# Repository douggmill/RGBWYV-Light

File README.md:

# RGBWYV-Light

RGBWYV-Light is a six-channel LED lamp — red, green, blue, white, amber, and violet — built around two [Seeed XIAO nRF52840](https://wiki.seeedstudio.com/XIAO_BLE/) boards. A Tkinter desktop console talks USB CDC at 921600 baud to a BLE central remote, which bridges newline-terminated ASCII commands over BLE UART to the peripheral light.

- [Features](#features)
- [Architecture](#architecture)
- [Hardware](#hardware)
- [Bill of materials](#bill-of-materials)
- [Hardware status](#hardware-status)
- [Serial command reference](#serial-command-reference)
- [Saved data format](#saved-data-format)
- [Building and flashing](#building-and-flashing)
- [Console](#console)
- [Repository layout](#repository-layout)
- [Roadmap](#roadmap)
- [Contributing](#contributing)
- [License](#license)

## Features

- Four operating modes:
  - **0 — Classic RGB:** a red–green–blue rainbow swell
  - **1 — Audio:** seven-band MSGEQ7 visualization; the white channel stays off
  - **2 — Manual:** direct mixer for all six channels and PWM frequency
  - **3 — Color Swells (retro):** red–green–violet color swells
- AHT20 temperature sensing
- Fan control through a PCF8574 I/O expander at address `0x20`, with automatic hysteresis (on at 35 °C, off at 32 °C) plus manual `fan0` / `fan1` commands
- Save and load of the 59 mixer parameters and the current mode to the light's internal filesystem

## Architecture

```mermaid
flowchart LR
    Console["Tkinter console"] -->|"USB CDC, 921600 baud"| Remote["BLE central remote<br/>XIAO nRF52840 Sense"]
    Remote -->|"BLE UART"| Light["Peripheral light<br/>XIAO nRF52840"]
    Light --> PWM["Six-channel PWM<br/>R, G, B, W, Amber, Violet"]
    Light --> EQ["MSGEQ7 audio"]
    Light --> Sens["AHT20 and PCF8574 fan"]
```

The central remote identifies itself as `LED Console 001` (manufacturer `Doug's Garage`). The light reports model `LED Device 001` over the BLE Device Information Service. The console auto-detects the remote by sending `*idn` and matching the reply in `config.ini`.

## Hardware

The light uses a Seeed XIAO nRF52840 (plain, not Sense). The remote uses a Seeed XIAO nRF52840 Sense, and in the current firmware it is only a USB-to-BLE bridge — the central sketch does not drive header GPIO.

**All MCU header pins are 3.3 V only and are not 5 V tolerant.** The MSGEQ7 and any logic tied to those pins must run at 3.3 V or be level-shifted.

### Peripheral pin map

Verified from `RGB_Peripheral_Device_R2/main/main.ino`. On the Seeeduino nRF52 core, Arduino pin `n` is header `Dn`.

| Function | Firmware | Header pin |
|----------|----------|------------|
| Red PWM | `RED_PIN 7` | D7 |
| Green PWM | `GREEN_PIN 2` | D2 |
| Blue PWM | `BLUE_PIN 8` | D8 |
| White PWM | `WHITE_PIN 6` | D6 |
| Amber PWM | `AMBER_PIN 9` | D9 |
| Violet PWM | `VIOLET_PIN 3` | D3 |
| MSGEQ7 analog out | `analogPin A0` | A0 (D0) |
| MSGEQ7 reset | `resetPin 1` | D1 |
| MSGEQ7 strobe | `strobePin 10` | D10 |
| I2C SDA / SCL | default `Wire` | D4 / D5 |
| PCF8574 | `pcf.begin(0x20, &Wire)` | address `0x20`; fan on expander pin 2 |
| AHT20 | `Adafruit_AHTX0` on `Wire` | same I2C bus |

KiCad schematics, PCB, and Gerbers are in `RGBYVW_Schematic_PCB/`. The board includes MOSFET LED drivers, the MSGEQ7, and an AHT20.

PWM frequency is set by `adc55` (a value of 1000 = 10 kHz maximum) and is applied in manual and audio modes.

## Bill of materials

Main light board (`nRF52840_RGBWYV`), generated by KiCad from the schematic and grouped by value and footprint (52 parts). The CSV is [`RGBYVW_Schematic_PCB/BOM.csv`](RGBYVW_Schematic_PCB/BOM.csv); per-schematic BOMs and ERC/DRC reports are in [`RGBYVW_Schematic_PCB/reports/`](RGBYVW_Schematic_PCB/reports/). The original hand-written BOM, including the mechanical parts, is [`BOM_R3_source.txt`](RGBYVW_Schematic_PCB/BOM_R3_source.txt).

| Qty | References | Value | Footprint |
|----:|------------|-------|-----------|
| 1 | AHT20 | Conn_01x04 | `Connector_PinHeader_2.54mm:PinHeader_1x04_P2.54mm_Vertical` |
| 1 | C1 | 100uF | `Capacitor_THT:CP_Radial_D10.0mm_P3.80mm` |
| 1 | C2 | 33pF CoG 50V 0402 | `Capacitor_SMD:C_0402_1005Metric_Pad0.74x0.62mm_HandSolder` |
| 1 | C3 | 0.1uF CoG 50V 0704 | `Capacitor_SMD:C_0603_1608Metric_Pad1.08x0.95mm_HandSolder` |
| 1 | C4 | 22uF-10uF | `Capacitor_SMD:C_0603_1608Metric_Pad1.08x0.95mm_HandSolder` |
| 4 | C5-C8 | 0.1uF XR7 0603 | `Capacitor_SMD:C_0603_1608Metric_Pad1.08x0.95mm_HandSolder` |
| 2 | D1, D3 | SDM05U20S3-7 20V 500mA | `Diode_SMD:D_SOD-323_HandSoldering` |
| 1 | D2 | 12 pin LED | `KiCad User Library:12 pin LED` |
| 1 | J1 | Screw_Terminal_01x02 | `TerminalBlock:TerminalBlock_Xinya_XY308-2.54-2P_1x02_P2.54mm_Horizontal` |
| 1 | J2 | Screw_Terminal_01x03 | `TerminalBlock:TerminalBlock_Xinya_XY308-2.54-3P_1x03_P2.54mm_Horizontal` |
| 1 | J3 | Conn_01x04 (screw terminal) | `TerminalBlock:TerminalBlock_Xinya_XY308-2.54-4P_1x04_P2.54mm_Horizontal` |
| 1 | J4 | Fan WINSINN 2010 | `Connector_JST:JST_XH_B2B-XH-A_1x02_P2.50mm_Vertical` |
| 7 | Q1-Q7 | IRLML6244 | `Package_TO_SOT_SMD:SOT-23` |
| 2 | R1, R3 | 22kΩ | `Resistor_SMD:R_0603_1608Metric_Pad0.98x0.95mm_HandSolder` |
| 1 | R2 | 221kΩ 0805 | `Resistor_SMD:R_0805_2012Metric_Pad1.20x1.40mm_HandSolder` |
| 9 | R4-R9, R17-R19 | 10kΩ | `Resistor_SMD:R_0603_1608Metric_Pad0.98x0.95mm_HandSolder` |
| 6 | R10-R15 | 4.7Ω | `Resistor_THT:R_Axial_DIN0309_L9.0mm_D3.2mm_P12.70mm_Horizontal` |
| 1 | R16 | 100Ω | `Resistor_SMD:R_0603_1608Metric_Pad0.98x0.95mm_HandSolder` |
| 1 | U1 | L7805 | `Package_TO_SOT_THT:TO-220-3_Horizontal_TabDown` |
| 1 | U2 | MSGEQ7 | `Package_DIP:DIP-8_W7.62mm` |
| 1 | U3 | PCF8574T | `Package_SO:SOIC-16W_7.5x10.3mm_P1.27mm` |
| 6 | U4-U9 | LM317_TO-220 | `Package_TO_SOT_THT:TO-220-3_Vertical` |
| 1 | U10 | nRF52840_XAIO | `A_USER_FOOTPRINTS:XAIO-nRF528400-TTH` |

`D2` and `U10` use the project's custom KiCad parts (`User` / `A_USER_Library` symbols, `KiCad User Library` / `A_USER_FOOTPRINTS` footprints). The symbols and footprints are embedded in the schematic and board files, so they open and plot without the libraries; the standalone library files are not in this repo.

### Mechanical / hardware

From [`BOM_R3_source.txt`](RGBYVW_Schematic_PCB/BOM_R3_source.txt). Dimensions, fits and assembly notes are in [`mechanical/README.md`](mechanical/README.md).

| Item | Value / PN | Qty | Notes | Link |
|------|------------|----:|-------|------|
| Wooden box | Amazon part | 1 | 95.5 × 87 × 62 mm outer, 3 mm floor, 22 mm lid | [Amazon](https://www.amazon.com/dp/B0B51L68YK) |
| Reflector cone | Amazon part | 1 | 48 mm mouth, 12 mm LED hole; cut to 29.2 mm (flush with the lid) | [Amazon](https://www.amazon.com/dp/B07MS8N2DS) |
| Fan 30 × 30 × 10 mm | Sunon MF30100V1-1000U-A99 | 1 | 5 V, 24 mm holes (check voltage vs the circuit) | [Digi-Key](https://www.digikey.com/en/products/detail/sunon-fans/MF30100V1-1000U-A99/10441403) |
| Fan grill, 3D printed | `mechanical/parts/fan_grill_30mm.stl` | 1 | 36 × 36 × 2 mm, outside of the floor | |
| M3 flat-head screws + thin nuts (grill) | ISO 10642 / DIN 439 | 4 + 4 | M3 × 18 (grill 2 + floor 3 + fan 10) | |
| 2.1 mm DC jack | uxcell a14103100ux0223 | 1 | 2.1 × 5.5, M8 panel mount, 20 mm overall | [Amazon](https://www.amazon.com/dp/B01C8CRCJ4) |
| USB-C breakout (horizontal) | Amabro | 1 | Plate glued in its wall pocket | [Amazon](https://www.amazon.com/dp/B0H9S9C73Q) |
| 3.5 mm stereo jack (TRS) | CESS 318 | 1 | M6 panel mount, 20 mm overall | [Amazon](https://www.amazon.com/dp/B00ZYWILMS) |
| Screw terminals 2.54 mm (J1 2P, J2 3P, J3 4P) | JSZAAHZ 46-pc kit | 1 kit | KF128/DG308-2.54 style | [Amazon](https://www.amazon.com/dp/B0FCXV6GT3) |
| AHT20 module | UMLIFE | 1 | 15.11 × 10.41 mm, 4-pin I2C | [Amazon](https://www.amazon.com/dp/B09B9ZWSDZ) |
| Male pin header 2.54 mm | 1 × 40 breakaway | 1 | 18 pins: XIAO 2 × 1x7, AHT20 1x4 | |
| Vent eyelets | chrome, 5 mm ID | 5 | already on the box | |
| Enclosure feet | source unknown | 4 | 5 mm dia × 5 mm | |
| M3 standoffs | M3 × 26 mm F-F | 4 | | |
| M3 button-head screws | | 4 | M3 × 5–6 mm (board to standoffs) | |
| M3 countersunk screws | | 4 | M3 × 8 mm (3 mm floor to standoffs) | |
| LED heatsink | uxcell 30 × 20 × 10 (10-pack) | 1 | pre-applied thermal pad | [Amazon](https://www.amazon.com/dp/B093V778LH) |
| TO-220 heatsink (LM317) | Adam Tech HSK-059-04 | 6 | 35 mm cut to 20 mm; U5/U7 fins filed to 5.0 mm | [Digi-Key](https://www.digikey.com/en/products/detail/adam-tech/HSK-059-04/26224094), [alt](https://www.amazon.com/gp/product/B0CG91KN14) |
| M3 screws (TO-220 sinks) | | 6 | M3 × 6 mm pan head | |
| Thermal paste | — | as needed | LM317 TO-220 tabs only | |
| Insulating thermal tape | 3M 8810 | 1 | LED pad — the pad is electrically live, so no paste or epoxy there | [Adafruit](https://www.adafruit.com/product/1467) |
| Epoxy | — | as needed | Not on the LED pad | |

## Hardware status

- **Main light board (`nRF52840_RGBWYV`)**: ERC has 0 errors and 11 warnings; DRC with schematic parity has 0 unconnected pads, 9 parity/footprint errors (the new fan-circuit parts that are not on the PCB yet), and 42 warnings. All other items are library warnings: footprints and symbols that differ from the newer KiCad 10 library copies, plus the custom libraries noted above.
- **Fan circuit (schematic only)**: an on-board PCF8574T (`U3`, I2C address `0x20`) drives fan pin P2 through `Q7`, a low-side IRLML6244. The circuit also adds the gate resistors `R16` and `R17`, the flyback diode `D3`, the JST-XH fan connector `J4` (WINSINN 2010, 5 V rail), the decoupling cap `C8`, and the I2C pull-ups `R18` and `R19`. These parts are **not on the PCB yet**; run *Tools → Update PCB from Schematic* in KiCad and place and route them. If an external PCF8574 module is still plugged into `J3`, remove it, because both would answer at `0x20`.
- **Controller (`nRF52840_Controller`)**: schematic only, no PCB yet. ERC has 0 errors and 3 warnings. The remaining warnings are the custom XIAO library, and the `BL` backlight label tied to 3V3 (intentional).
- **`RGBYVW_R2`**: a superseded draft that `nRF52840_RGBWYV` replaces. Its schematic ERC is down to 0 errors, but its PCB has known layout problems (shorts, clearance violations, duplicate footprints, unrouted nets). It is kept for reference only; don't fabricate it.

## Serial command reference

Commands are newline-terminated ASCII. Carriage returns are ignored, so CRLF is treated as a single line. The console and the central speak USB CDC at 921600 baud. The central handles a short local command set and, when a BLE connection is up, forwards every other complete line to the light over BLE UART.

### Central (USB)

| Command | Action |
|---------|--------|
| `*idn` | Print the central name (`LED Console 001`) |
| `help` | Print the command menu |
| `info` | Print the connected peripheral's manufacturer and model |

### Peripheral (via the central)

| Command | Action |
|---------|--------|
| `adcN,V` | Set parameter `N` (0–58) to `V`, where `V` is 0–1000 (1000 = 1.0) |
| `mode,0` … `mode,3` | Select a mode. All six PWM channels are zeroed on a mode change; manual mode then applies the current mix |
| `save` | Write the current 59 `adc[]` values and the mode to `data.txt` |
| `read` | Print the saved file and reload it into RAM |
| `val?` | Print the live RAM snapshot (59 values plus mode) |
| `dele` | Delete the saved `data.txt` file |
| `temp` | Print the AHT20 temperature in Celsius |
| `fan0` / `fan1` | Turn the fan off or on and update the stored fan state |
| `err?` | Print I2C health: `tempI2C=` and `fanI2C=` (`1` = good, `0` = bad) |

### `adc` parameter map

**Audio mode** (seven MSGEQ7 bands: 63 Hz, 160 Hz, 400 Hz, 1 kHz, 2.5 kHz, 6.25 kHz, 16 kHz):

| Channels | Meaning |
|----------|---------|
| `adc0`–`adc6` | Red mixer, one weight per band |
| `adc7`–`adc13` | Amber mixer |
| `adc14`–`adc20` | Green mixer |
| `adc21`–`adc27` | Blue mixer |
| `adc28`–`adc34` | Violet mixer |
| `adc35`–`adc41` | Upper thresholds |
| `adc42`–`adc48` | Lower thresholds |

**Manual mode:**

| Channel | Meaning |
|---------|---------|
| `adc49` | Red |
| `adc50` | Amber |
| `adc51` | Green |
| `adc52` | Blue |
| `adc53` | Violet |

**Classic RGB and color swells:**

| Channel | Meaning |
|---------|---------|
| `adc56` | Speed |
| `adc57` | Pastel / white level |
| `adc58` | Brightness (color amplitude) |

**Always present:**

| Channel | Meaning |
|---------|---------|
| `adc54` | White LED (held at zero while audio mode is running) |
| `adc55` | PWM frequency, 10 kHz max (1000 = 10 kHz) |

## Saved data format

`save` writes one CSV schema: all 59 `adc[]` values as thousandths, then the mode integer. `val?` uses the same layout from live RAM.

`data.txt` files written by the older R2 firmware use a different scale for channels 49–55. After flashing this firmware, set the sliders you care about and send **Save** once (or `dele` followed by `save`) before trusting a restored mix.

## Building and flashing

Use the **Seeed nRF52 Boards** core (`Seeeduino:nrf52` 1.1.13), not the Adafruit nRF52 package and not “Seeed nRF52 mbed-enabled Boards.” The mbed core numbers D6–D10 differently; this firmware uses bare pin integers, so a mbed build would drive the wrong pads.

Board manager URL:

```text
https://files.seeedstudio.com/arduino/package_seeeduino_boards_index.json
```

```bash
arduino-cli config add board_manager.additional_urls https://files.seeedstudio.com/arduino/package_seeeduino_boards_index.json
arduino-cli core update-index
arduino-cli core install Seeeduino:nrf52@1.1.13
```

Libraries required by the peripheral sketch:

- nRF52_PWM
- Adafruit PCF8574
- Adafruit AHTX0
- Adafruit Unified Sensor
- Adafruit BusIO

`bluefruit.h`, LittleFS, and InternalFileSystem ship with the Seeed nRF52 core. `adafruit-nrfutil` and a `python` interpreter on `PATH` are needed to package the DFU zip after compile.

```bash
arduino-cli lib install "nRF52_PWM" "Adafruit PCF8574" "Adafruit AHTX0" "Adafruit Unified Sensor" "Adafruit BusIO"
```

Compile each sketch for its own board. Do not swap the FQBNs.

```bash
# Peripheral light — plain XIAO nRF52840
arduino-cli compile --fqbn Seeeduino:nrf52:xiaonRF52840 \
  --output-dir ./build-light \
  RGB_Peripheral_Device_R2/main

# Central remote — XIAO nRF52840 Sense
arduino-cli compile --fqbn Seeeduino:nrf52:xiaonRF52840Sense \
  --output-dir ./build-remote \
  RGB_Central_Remote_R2/RGB_Central_Remote_R2
```

Flash the DFU packages over USB serial. Replace the port with the board's CDC device (`/dev/ttyACM0`, `/dev/tty.usbmodem*`, or `COMx`). The bootloader DFU rate is 115200, independent of the 921600 application baud.

```bash
adafruit-nrfutil dfu serial -pkg ./build-light/main.ino.zip -p /dev/ttyACM0 -b 115200 --touch 1200
adafruit-nrfutil dfu serial -pkg ./build-remote/RGB_Central_Remote_R2.ino.zip -p /dev/ttyACM1 -b 115200 --touch 1200
```

`--touch 1200` pulses the port at 1200 baud so the XIAO enters the bootloader. If that handshake fails, double-tap the board's reset button and run the same command again.

## Console

The desktop console lives in `console.py/`. It is a Python 3 Tkinter app (ttk `clam` theme) with light and dark modes, a serial transcript, and four tabs that match the firmware modes: Manual Color Mixer, Classic RGB, Audio Effect, and Color Swells.

### Requirements

- Python 3
- tkinter (a system package on many Linux distributions, for example `python3-tk`)
- [pyserial](https://pypi.org/project/pyserial/)
- [Pillow](https://pypi.org/project/Pillow/)

```bash
python3 -m pip install pyserial pillow
```

### Running

```bash
git clone https://github.com/douggmill/RGBWYV-Light.git
cd RGBWYV-Light/console.py
python3 main.py
```

On startup the console scans serial ports (preferring `/dev/ttyACM*`, then macOS `usbmodem` devices, then `COM` ports), sends `*idn`, and connects when the reply matches `config.ini`.

`console.py/config.ini`:

```ini
[Settings]
idn = LED Console 001
theme = dark
```

`theme` may be `dark` or `light`. The window toggle and the View menu write this key back. **File → Open Config** opens the file in the system editor; **File → Save Values** and the **Save** button send `save` to the light. **Help** sends `help`.

## Repository layout

```text
RGBWYV-Light/
  console.py/                      Desktop console
    main.py                        UI, sliders, and theme
    serial_module.py               USB CDC and *idn autodetect
    ini.py, config.ini             IDN string and saved theme
  RGB_Central_Remote_R2/           Firmware for the BLE remote
    RGB_Central_Remote_R2/
  RGB_Peripheral_Device_R2/        Firmware for the light
    main/
  RGBYVW_Schematic_PCB/            KiCad schematic, PCB, and Gerbers
  mechanical/                      FreeCAD assembly, STEP models, renders, printable fan grill
  old/RGBWYV_R2/                   Archived R2 snapshot
  docs/images/                     README photos
```

`old/` is the archived R2 tree, kept for reference. It is not the firmware or console you should build.

## Roadmap

This is a working R3 of a personal lighting project. Further firmware and console changes are expected. Follow-ups include tightening the serial protocol and cleaning up leftover prototype files under `console.py/old/`.

## Contributing

Issues and pull requests are welcome. Please describe the change, test against the hardware when you can, and keep command and pin behavior consistent with the firmware in this repository.

## License

License: not yet specified.

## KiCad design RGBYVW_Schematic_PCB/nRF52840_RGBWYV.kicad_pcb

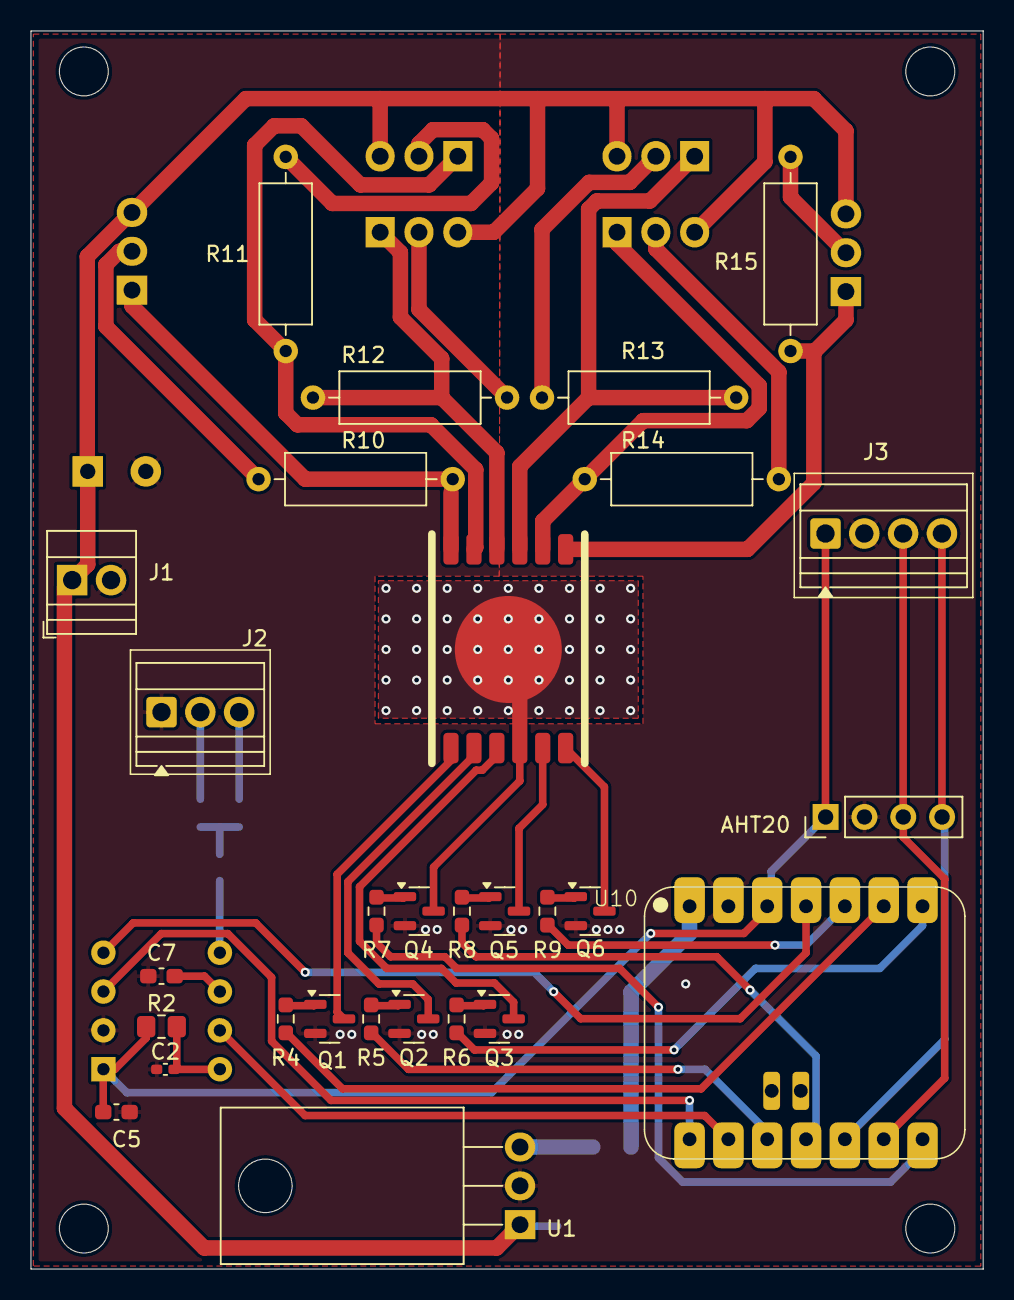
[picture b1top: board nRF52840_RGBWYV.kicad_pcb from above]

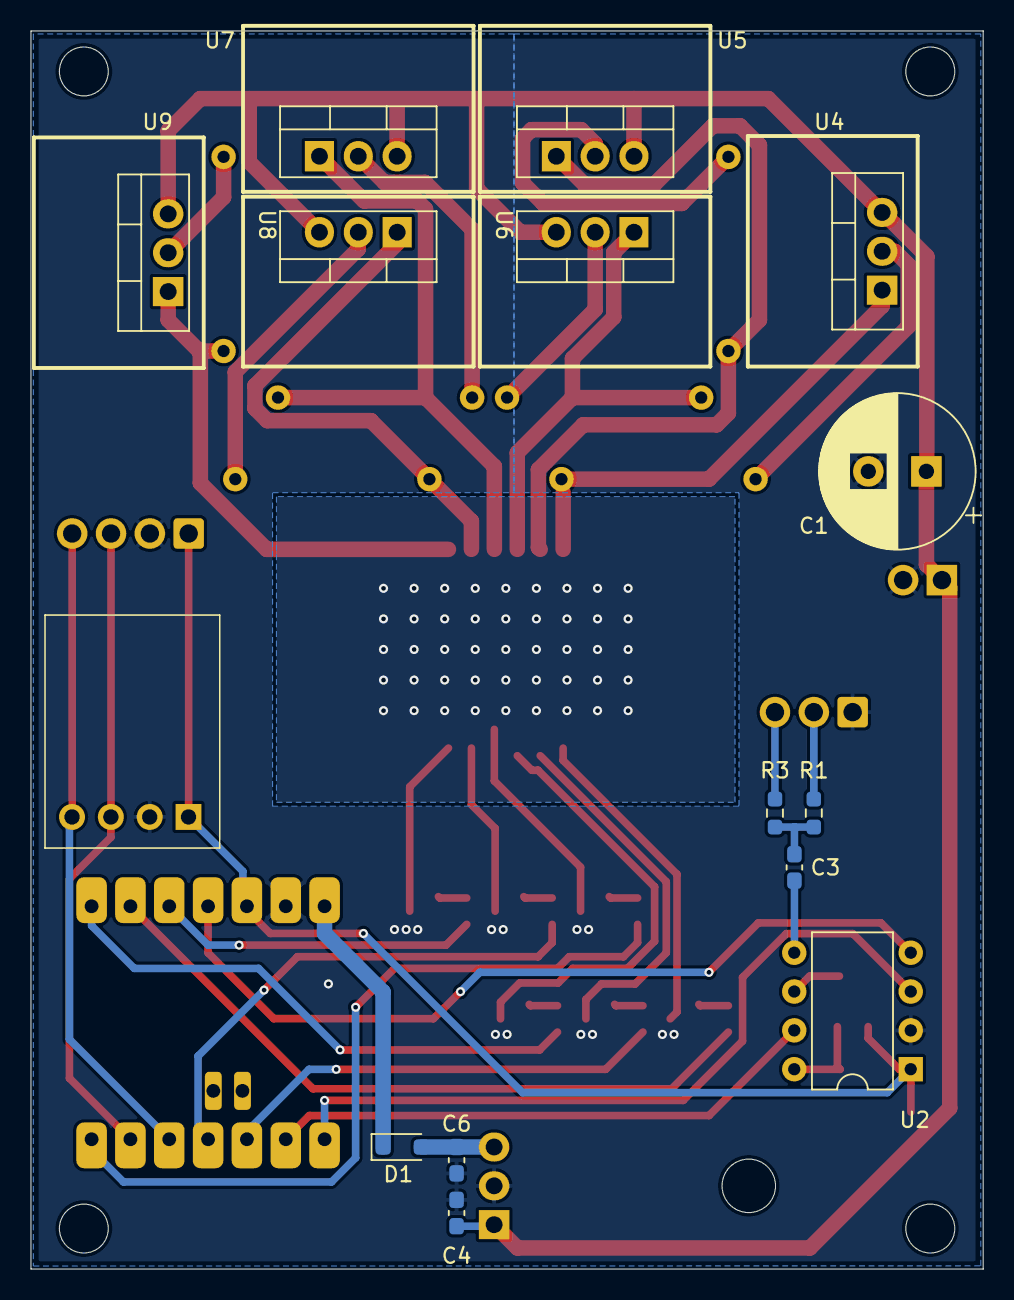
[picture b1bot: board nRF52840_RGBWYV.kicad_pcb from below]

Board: 2 copper layers, 62.3 x 81.0 mm, 47 parts (14 on the bottom side), 46 nets.

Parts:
AHT20: Conn_01x04; PinHeader_1x04_P2.54mm_Vertical
C1: 100uF; CP_Radial_D10.0mm_P3.80mm
C2: 33pF CoG 50V 0402; C_0402_1005Metric_Pad0.74x0.62mm_HandSolder
C3: 0.1uF CoG 50V 0704; C_0603_1608Metric_Pad1.08x0.95mm_HandSolder
C4: 22uF-10uF; C_0603_1608Metric_Pad1.08x0.95mm_HandSolder
C5, C6, C7: 0.1uF XR7 0603; C_0603_1608Metric_Pad1.08x0.95mm_HandSolder
D1: SDM05U20S3-7 20V 500mA; D_SOD-323_HandSoldering
D2: 12 pin LED
H1, H2, H3, H4: MountingHole_3.2mm_M3
J1: Screw_Terminal_01x02; TerminalBlock_Xinya_XY308-2.54-2P_1x02_P2.54mm_Horizontal
J2: Screw_Terminal_01x03; TerminalBlock_Xinya_XY308-2.54-3P_1x03_P2.54mm_Horizontal
J3: Conn_01x04; TerminalBlock_Xinya_XY308-2.54-4P_1x04_P2.54mm_Horizontal
Q1, Q2, Q3, Q4, Q5, Q6: IRLML6244; SOT-23
R1, R3: 22kΩ; R_0603_1608Metric_Pad0.98x0.95mm_HandSolder
R2: 221kΩ 0805; R_0805_2012Metric_Pad1.20x1.40mm_HandSolder
R4, R5, R6, R7, R8, R9: 10kΩ; R_0603_1608Metric_Pad0.98x0.95mm_HandSolder
R10, R11, R12, R13, R14, R15: 4.7Ω; R_Axial_DIN0309_L9.0mm_D3.2mm_P12.70mm_Horizontal
U1: L7805; TO-220-3_Horizontal_TabDown
U2: MSGEQ7; DIP-8_W7.62mm
U4, U5, U6, U7, U8, U9: LM317_TO-220; TO-220-3_Vertical
U10: nRF52840_XAIO; XAIO-nRF528400-TTH

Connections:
3V3: AHT20.1, C5.1, J3.1, R2.2, U2.1 (VDD), U10.3 (3V3)
5V: D1.1 (K), U10.1 (5V)
12V: C1.1, C4.1, J1.1, U1.1 (IN), U4.3 (VI), U5.3 (VI), U6.3 (VI), U7.3 (VI), U8.3 (VI), U9.3 (VI)
AMBER: R9.1, U10.5 (D9/MISO)
BLUE: R4.1, U10.6 (D8/SCK)
GNDREF: AHT20.2, C1.2, C2.1, C4.2, C5.2, C6.2, C7.2, J1.2, J2.1, J3.2, Q1.2 (S), Q2.2 (S), Q3.2 (S), Q4.2 (S), Q5.2 (S), Q6.2 (S), U1.2 (GND), U2.2 (VSS), U10.2 (GND)
GREEN: R5.1, U10.12 (A2/D2)
unnamed: C3.1, R1.1, R3.1
unnamed: C6.1, D1.2 (A), U1.3 (OUT)
unnamed: J2.2, R1.2
unnamed: J2.3, R3.2
unnamed: D2.1, Q1.3 (D)
unnamed: Q1.1 (G), R4.2
unnamed: D2.2, Q2.3 (D)
unnamed: Q2.1 (G), R5.2
unnamed: D2.3, Q3.3 (D)
unnamed: Q3.1 (G), R6.2
unnamed: D2.4, Q4.3 (D)
unnamed: Q4.1 (G), R7.2
unnamed: D2.5, Q5.3 (D)
unnamed: Q5.1 (G), R8.2
unnamed: D2.6, Q6.3 (D)
unnamed: Q6.1 (G), R9.2
unnamed: C2.2, R2.1, U2.8 (CKIN)
unnamed: C7.1, U2.6 (GND)
unnamed: C3.2, U2.5 (IN)
unnamed: D2.12, R10.2, U4.1 (ADJ)
unnamed: R10.1, U4.2 (VO)
unnamed: D2.11, R11.2, U5.1 (ADJ)
unnamed: R11.1, U5.2 (VO)
unnamed: D2.10, R12.2, U6.1 (ADJ)
unnamed: R12.1, U6.2 (VO)
unnamed: D2.9, R13.2, U7.1 (ADJ)
unnamed: R13.1, U7.2 (VO)
unnamed: D2.8, R14.2, U8.1 (ADJ)
unnamed: R14.1, U8.2 (VO)
unnamed: D2.7, R15.2, U9.1 (ADJ)
unnamed: R15.1, U9.2 (VO)
unnamed: U2.3 (OUT), U10.14 (A0/D0)
unnamed: U2.7 (RESET), U10.13 (A1/D1)
unnamed: U2.4 (STROBE), U10.4 (D10/MOSI)
RED: R6.1, U10.7 (D7/RX)
SCL: AHT20.3, J3.3, U10.9 (A5/D5)
SDA: AHT20.4, J3.4, U10.10 (A4/D4)
VIOLET: R8.1, U10.11 (A3/D3)
WHITE: R7.1, U10.8 (D6)

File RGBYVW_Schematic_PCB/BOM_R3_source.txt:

Reference			Value			Qty
AHT20				Conn_01x04		1
C1				100uF			1
C2,				33pF CoG 50V 0402	1
C3				0.1uF CoG 50V 0704	1
C4				22uF-10uF		1
"C5,C6,C7"			0.1uF XR7 0603		3
D1				SDM05U20S3-7 20V 500mA	1
D2				12 pin LED		1
J1				Screw_Terminal_01x02	1
J2				Screw_Terminal_01x03	1
J3				Screw_Terminal_01x04	1
"Q1,Q2,Q3,Q4,Q5,Q6"		IRLML6244		6
"R1,R3"				22kΩ 0603		2
R2				221kΩ 0805		1
"R4,R5,R6,R7,R8,R9"		10kΩ 0603		6
"R10,R11,R12,R13,R14,R15"	4.7Ω			6
U1				L7805			1
U2				MSGEQ7 DIP-8		1
"U4,U5,U6,U7,U8,U9"		LM317_TO-220		6
U10				nRF52840_XAIO		1

Hardware:
Item					Value/PN				Qty	Dimensions / Rating / Notes			Link
Wooden Box				Amazon part				1	95.5 x 87 x 62mm outer (3.75" x 3 1/8" x 2.5")	https://www.amazon.com/dp/B0B51L68YK
Reflector Cone				Amazon part				1	48mm mouth, 12mm LED hole; shorten to 27.8mm (flush with lid)	https://www.amazon.com/dp/B07MS8N2DS
Fan 30x30x10mm				Sunon MF30100V1-1000U-A99		1	5VDC 0.6W 5.5CFM, 24mm holes (check voltage vs circuit)	https://www.digikey.com/en/products/detail/sunon-fans/MF3010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
Fan Grill, 3D printed (PLA/PETG)	mechanical/parts/fan_grill_30mm.stl	1	36 x 36 x 2mm, outside of floor
M3 Flat Head Screws (fan grill)		ISO 10642 / DIN 7991			4	M3 x 22mm (grill 2 + floor 7 + fan 10)
M3 Thin Nuts (fan grill)		DIN 439					4	M3, 1.8mm thick, on top of the fan
2.1mm DC Power Jack			uxcell B01C8CRCJ4			1	Chassis mount, threaded, >3A			https://www.amazon.com/dp/B01C8CRCJ4
USB-C Breakout Board (horizontal)	Amabro B0H9S9C73Q			1	Chassis mount, slot horizontal; plate glued in its inside wall pocket (no face screws)	https://www.amazon.com/dp/B0H9S9C73Q
3.5mm Stereo Audio Jack (TRS)		CESS 318 B00ZYWILMS			1	Panel mount, M6 thread, solder lugs; $6.99 per 5-pack	https://www.amazon.com/dp/B00ZYWILMS
Screw Terminals 2.54mm pitch (J1 2P, J2 3P, J3 4P)	JSZAAHZ 46-pc kit B0FCXV6GT3	1	KF128/DG308-2.54 style, 150V 6A, 26-18AWG; $14.99 kit (uses 1x 2P, 1x 3P, 1x 4P); dims assumed from XY308-2.54	https://www.amazon.com/dp/B0FCXV6GT3
AHT20 Temp/Humidity Module		UMLIFE B09B9ZWSDZ			1	15.11 x 10.41mm, 4-pin 2.54mm I2C		https://www.amazon.com/dp/B09B9ZWSDZ
Male Pin Header 2.54mm, breakaway 1x40	PN?					1	18 pins used: XIAO 2 x 1x7 + AHT20 1x4, 2.54mm plastic
Vent Eyelets (connector face)		chrome, 5mm ID				5	Already on Doug's box
Enclosure Feet				source unknown				4	5mm dia x 5mm tall; grill sits 3mm above the table
M3 Standoffs				PN?					4	23.4mm measured (non-standard): M3x23 + 0.4mm washer, or stack M3x20 + M3x3
M3 Button Head Screws			PN?					4	M3 x 5-6mm (board to standoffs)
M3 Countersunk Screws			PN?					4	M3 x 12mm (floor to standoffs)

Heatsink:
Item					Value/PN				Qty	Dimensions / Notes				Link
LED Heatsink				uxcell 30x20x10 (10-pack)		1	$9.99 per 10-pack, blue, pre-applied thermal pad	https://www.amazon.com/dp/B093V778LH
TO-220 Heatsink (LM317)			Adam Tech HSK-059-04			6	$1.37 ea, 35mm cut to 20mm; U5/U7 fin tips filed to 5.0mm; Digi-Key 2057-HSK-059-04-ND	https://www.digikey.com/en/products/detail/adam-tech/HSK-059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
											alt: https://www.amazon.com/gp/product/B0CG91KN14
M3 Screws (TO-220 sinks)		PN?					6	M3 x 6mm pan head into the sink's tapped hole (tab is live: keep sinks apart)
Thermal Paste				-					A/R	LM317 TO-220 tabs only
3M 8810 Insulating Thermal Tape		3M 8810					1	LED pad (pad is electrically live - no paste or epoxy there)	https://www.adafruit.com/product/1467
Epoxy					-					A/R	Not on LED pad (use 3M 8810 tape there)

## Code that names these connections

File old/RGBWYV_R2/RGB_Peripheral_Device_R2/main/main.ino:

////////////////////////////////////////////////////////////////////////////////////////////////////////////////
//////////////////////////////////////////////Perpheral Device/////////////////////////////////////////////////
//////////////////////////////////////////////////////////////////////////////////////////////////////////////
// BEFORE including <nRF52_PWM.h>
#ifdef _PWM_LOGLEVEL_
#undef _PWM_LOGLEVEL_
#endif
#define _PWM_LOGLEVEL_ 0
#include <nRF52_PWM.h>
#include <bluefruit.h>
#include <Adafruit_PCF8574.h>
#include <Adafruit_AHTX0.h>
#include <Adafruit_LittleFS.h>
#include <InternalFileSystem.h>

//---------Programable Button--------------//



#define _PWM_LOGLEVEL_ 0
#define USING_TIMER false  // Select false to use PWM

#define analogPin A0
#define resetPin 1
#define strobePin 10

#define NUM_OF_PINS 6

#define GREEN_PIN 2
#define RED_PIN 7
#define BLUE_PIN 8

#define AMBER_PIN 9
#define VIOLET_PIN 3
#define WHITE_PIN 6

float spectrumValues[7];  // Array to hold amplitude values for each band
float adcValue = 0.0;
float adcValueResolution = 1023.0;  // 10bit for nRF52840 Ainputs
float percentage = 0.0;

float adc[59] = {
  1.0, 0.0, 0.0, 0.0, 0.0, 0.0, 0.0,   // redMultipliers
  0.0, 0.0, 0.0, 0.0, 0.0, 0.0, 0.0,   // amberMultipliers
  0.0, 1.0, 0.0, 0.0, 0.0, 0.0, 0.0,   // greenMultipliers
  0.0, 0.0, 1.0, 0.0, 0.0, 0.0, 0.0,   // blueMultipliers
  0.0, 0.0, 0.0, 0.5, 0.5, 0.0, 0.0,   // violetMultipliers
  1.0, 1.0, 1.0, 1.0, 1.0, 1.0, 1.0,   // upperTresholds
  0.1, 0.1, 0.1, 0.1, 0.1, 0.1, 0.1,   // lowerThresholds
  0.0, 0.0, 0.0, 0.0, 0.0, 0.0, 0.50,  // manualValues R,Y,G,B,V,W,freq
  0.0, 0.0, 0.0                        // rainbow (wave) effect
};

float redMultipliers[7] = { adc[0], adc[1], adc[2], adc[3], adc[4], adc[5], adc[6] };
float amberMultipliers[7] = { adc[7], adc[8], adc[9], adc[10], adc[11], adc[12], adc[13] };
float greenMultipliers[7] = { adc[14], adc[15], adc[16], adc[17], adc[18], adc[19], adc[20] };
float blueMultipliers[7] = { adc[21], adc[22], adc[23], adc[24], adc[25], adc[26], adc[27] };
float violetMultipliers[7] = { adc[28], adc[29], adc[30], adc[31], adc[32], adc[33], adc[34] };
float upperThresholds[7] = { adc[35], adc[36], adc[37], adc[38], adc[39], adc[40], adc[41] };
float lowerThresholds[7] = { adc[42], adc[43], adc[44], adc[45], adc[46], adc[47], adc[48] };
float RYGBVW_Values[6] = { adc[49], adc[50], adc[51], adc[52], adc[53], adc[54] };  // used for manualControl (adc[chan]*100.0)
float whiteValue = adc[54] * 100.0;                                                 // can be manually addjusted in any effect mode
float frequency = adc[55] * 10000.00;                                               // 10kHz max, initial value set to 1khz for now
float multiplierSums[5] = { 0.0, 0.0, 0.0, 0.0, 0.0 };

float dutyCycleValues[NUM_OF_PINS] = { 0.0, 0.0, 0.0, 0.0, 0.0, 0.0 };                           // Ensure it's initialized properly
int PWM_Pins[NUM_OF_PINS] = { RED_PIN, AMBER_PIN, GREEN_PIN, BLUE_PIN, VIOLET_PIN, WHITE_PIN };  // Array of pins for PWM
int effectModes = 1;                                                                             // 0 == wave, 1 == music, 2 == manual              // 0 = manualControl, 1 = audioEffect, else = off

String allValuesCSV = "";

//-----------------------------------rainbow effect-------------------------------------------//

int phaseIndexRain = 0;                      // Initial phase index for rav_wav
float colorIndexRain = 0.0;                  // Variable to track color transition within each phase
unsigned long previousMillisEffectRain = 0;  // Common previousMillis for all phases
unsigned long intervalEffectRain = 0;        // Default interval, will be updated dynamically

//-----------------------------------Constants-------------------------------------------//
const int BUFFER_SIZE = 256;  // Adjust size as needed
const int BUFFER_SIZE2 = 32;  // Adjust size as needed
const char Manufacturer[] = "Doug's Garage";
const char Model[] = "LED Device 001";
const float dutyCycleOffValue = 0.0;

//---------------------------------Command Buffers----------------------------------------//

char input[BUFFER_SIZE];    // serial buffer
char output[BUFFER_SIZE2];  // ble output buffer
bool BLEisConnected = false;

//--------------------------------------TempFan----------------------------------------//

float fanOnTemp = 35.00;  // in degC
float fanOffTemp = 32.00;
bool fanState = 0;
unsigned long temp_Sample_Delay = 30000;  // 30 sec
unsigned long previousMillis = 0;
bool statusI2C_1 = 0;
bool statusI2C_2 = 0;

//--------------------------------initialize objects---------------------------------//
using namespace Adafruit_LittleFS_Namespace;
File file(InternalFS);
nRF52_PWM* PWM_Instances[NUM_OF_PINS];
BLEUart bleuart;
BLEDis bledis;
Adafruit_AHTX0 aht;
Adafruit_PCF8574 pcf;

//--------------------------------function prototypes---------------------------------//

void handleComms();
void setupAudioEffect();
void setupPWM();
void setupBLE_Peripheral();
void audioEffect();
void setupAHT20TempSensor();
void setupPCF8574();
void timedFunctions();
void RainbowEffect(float value1, float value2, float value3);
// void setupSerial();
void setupInternalFS();

void setup() {

  // analogReadResolution(12);
  // setupSerial();
  setupAudioEffect();
  setupPWM();
  setupPCF8574();
  setupAHT20TempSensor();
  setupInternalFS();

  /////////////////////////// Put BLE Setup Last!!! ////////////////////////////////////
  setupBLE_Peripheral();

  if (effectModes == 2) {
    writeManual();
  }
}

void loop() {
  if (BLEisConnected && bleuart.available()) {
    handleComms();  // Run only when communication is received
  }
  if (effectModes == 0) {
    Rainbow_Classic(adc[56], adc[57], adc[58]);
  }
  if (effectModes == 1) {
    audioEffect();
  }
  if (effectModes == 3) {
    RetroEffect(adc[56], adc[57], adc[58]);
  }

  timedFunctions();
}
